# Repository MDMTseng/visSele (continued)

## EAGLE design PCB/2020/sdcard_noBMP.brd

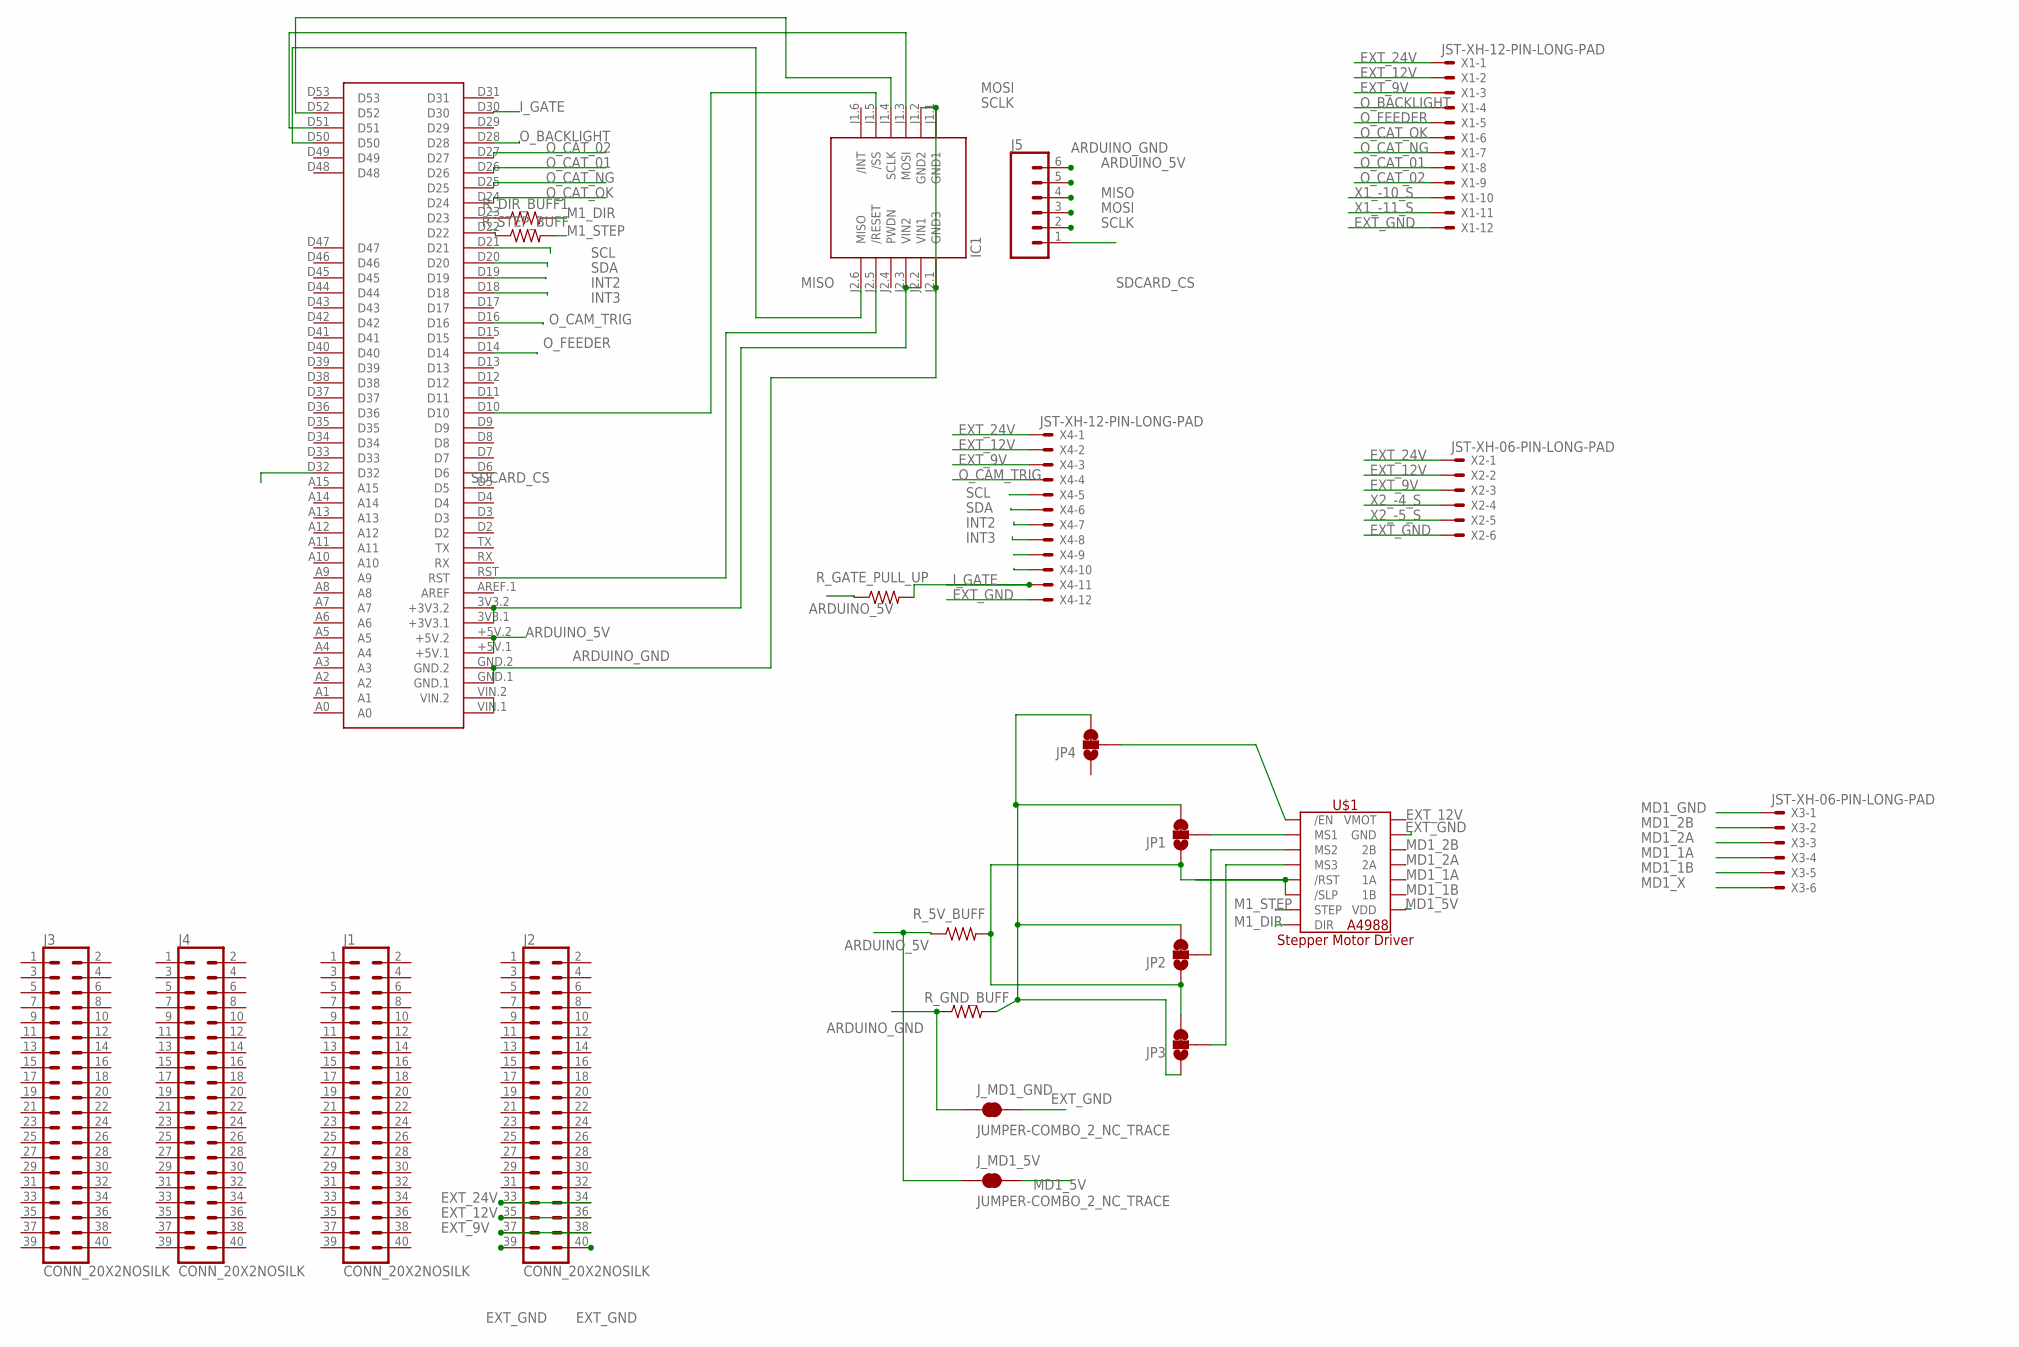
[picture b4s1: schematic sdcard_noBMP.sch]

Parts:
IC1: WIZ820IO_DEVICE'DUAL-IN-LINE'; WIZ820IO
J1, J2, J3, J4: CONN_20X2NOSILK; 2X20_NOSILK
J5: CONN_06LOCK; 1X06_LOCK
JP1, JP2, JP3, JP4: JUMPER-SMT_3_1-NC_TRACE_NO-SILK; SMT-JUMPER_3_1-NC_TRACE_NO-SILK
J_MD1_5V, J_MD1_GND: JUMPER-COMBO_2_NC_TRACE; COMBO-JUMPER_2_NC_TRACE
R_5V_BUFF: 1k; 0402-TIGHT
R_DIR_BUFF1: 1k; 0402-TIGHT
R_GATE_PULL_UP: 1k; 0402-TIGHT
R_GND_BUFF: 1k; 0402-TIGHT
R_STEP_BUFF: 1k; 0402-TIGHT
U$1: A4988_STEP
U$2: MEGA2560_MIKRO
X1, X4: JST-XH-12-PIN-LONG-PAD; JST-XH-12-PACKAGE-LONG-PAD
X2, X3: JST-XH-06-PIN-LONG-PAD; JST-XH-06-PACKAGE-LONG-PAD

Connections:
ARDUINO_5V: J5.5, J_MD1_5V.1, J_MD1_5V.3 (1), R_5V_BUFF.1, R_GATE_PULL_UP.1, U$2.+5V.1, U$2.+5V.2
ARDUINO_GND: IC1.J1.1 (GND1), IC1.J1.2 (GND2), IC1.J2.1 (GND3), J5.6, J_MD1_GND.1, J_MD1_GND.3 (1), R_GND_BUFF.1, U$2.GND.1, U$2.GND.2
EXT_9V: J2.37, J2.38, U$2.VIN.1, U$2.VIN.2, X1.3, X2.3, X4.3
EXT_12V: J2.35, J2.36, U$1.VMOT, X1.2, X2.2, X4.2
EXT_24V: J2.33, J2.34, X1.1, X2.1, X4.1
EXT_GND: J2.39, J2.40, J_MD1_GND.2, J_MD1_GND.4 (2), U$1.GND, U$1.GND2 (GND), X1.12, X2.6, X4.12
INT2: U$2.D19, X4.7
INT3: U$2.D18, X4.8
I_GATE: R_GATE_PULL_UP.2, U$2.D30, X4.11
M1_DIR: R_DIR_BUFF1.2, U$1.DIR
M1_STEP: R_STEP_BUFF.2, U$1.STEP
MD1_1A: U$1.1A, X3.4
MD1_1B: U$1.1B, X3.5
MD1_2A: U$1.2A, X3.3
MD1_2B: U$1.2B, X3.2
MD1_5V: J_MD1_5V.2, J_MD1_5V.4 (2), U$1.VDD
MD1_GND: X3.1
MD1_X: X3.6
MISO: IC1.J2.6 (MISO), J5.4, U$2.D50
MOSI: IC1.J1.3 (MOSI), J5.3, U$2.D51
unnamed: JP1.1, JP2.1, JP3.3, R_5V_BUFF.2, U$1./RST, U$1./SLP
unnamed: IC1.J1.5 (/SS), U$2.D10
unnamed: R_STEP_BUFF.1, U$2.D22
unnamed: IC1.J2.5 (/RESET), U$2.RST
unnamed: IC1.J2.2 (VIN1), IC1.J2.3 (VIN2), U$2.3V3.1 (+3V3.1), U$2.3V3.2 (+3V3.2)
unnamed: JP1.2, U$1.MS1
unnamed: JP2.2, U$1.MS2
unnamed: JP3.2, U$1.MS3
unnamed: JP4.2, U$1./EN
unnamed: JP1.3, JP2.3, JP3.1, JP4.3, R_GND_BUFF.2
unnamed: R_DIR_BUFF1.1, U$2.D23
O_BACKLIGHT: U$2.D28, X1.4
O_CAM_TRIG: U$2.D16, X4.4
O_CAT_01: U$2.D26, X1.8
O_CAT_02: U$2.D27, X1.9
O_CAT_NG: U$2.D25, X1.7
O_CAT_OK: U$2.D24, X1.6
O_FEEDER: U$2.D14, X1.5
SCL: U$2.D21, X4.5
SCLK: IC1.J1.4 (SCLK), J5.2, U$2.D52
SDA: U$2.D20, X4.6
SDCARD_CS: J5.1, U$2.D32
X1_-10_S: X1.10
X1_-11_S: X1.11
X2_-4_S: X2.4
X2_-5_S: X2.5

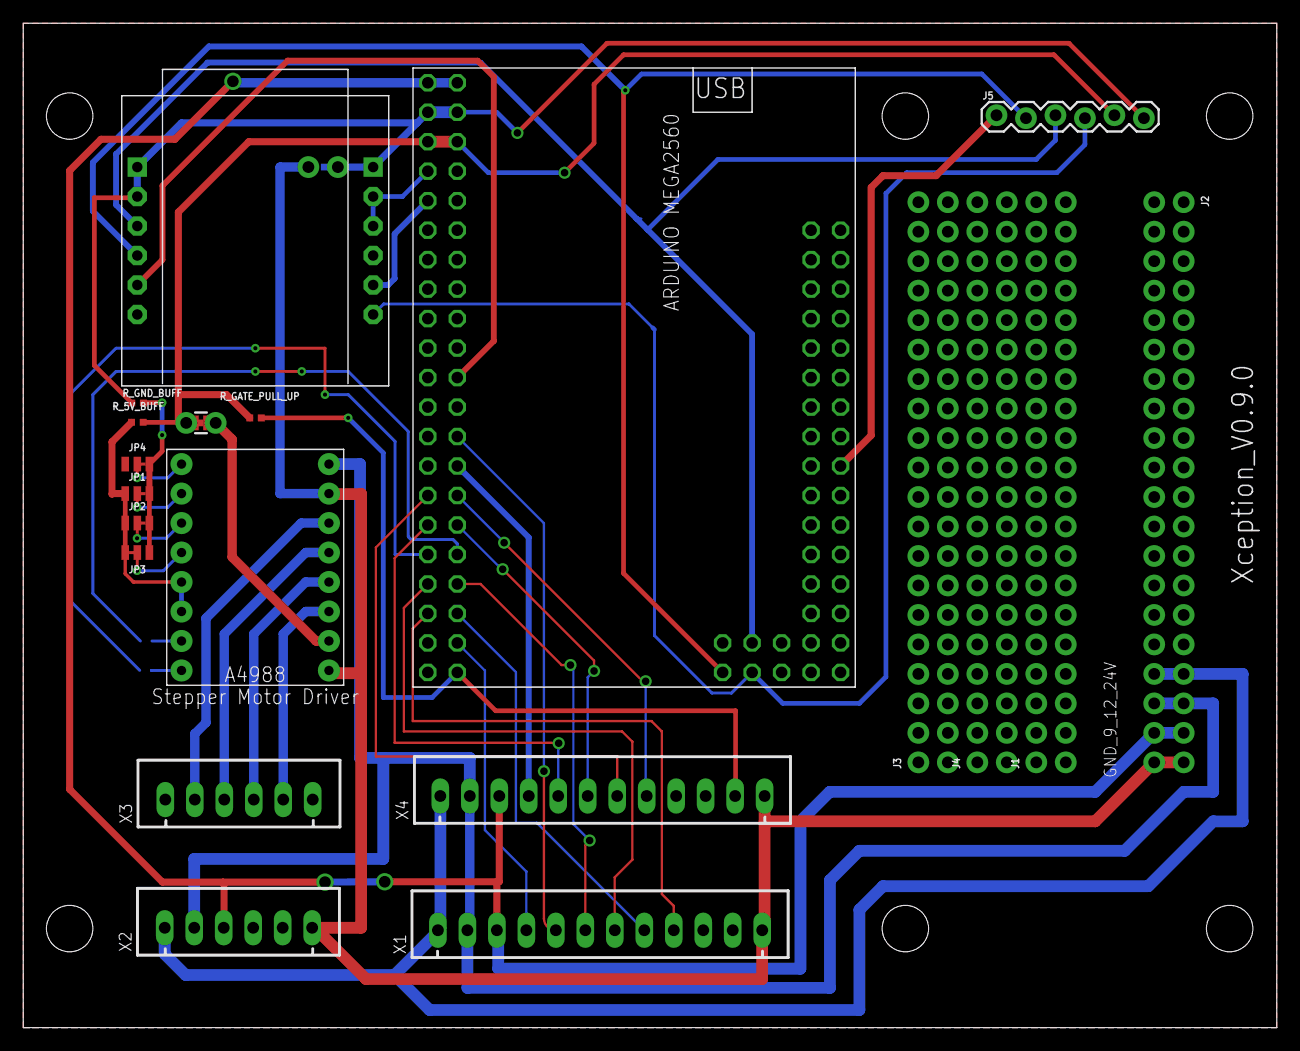
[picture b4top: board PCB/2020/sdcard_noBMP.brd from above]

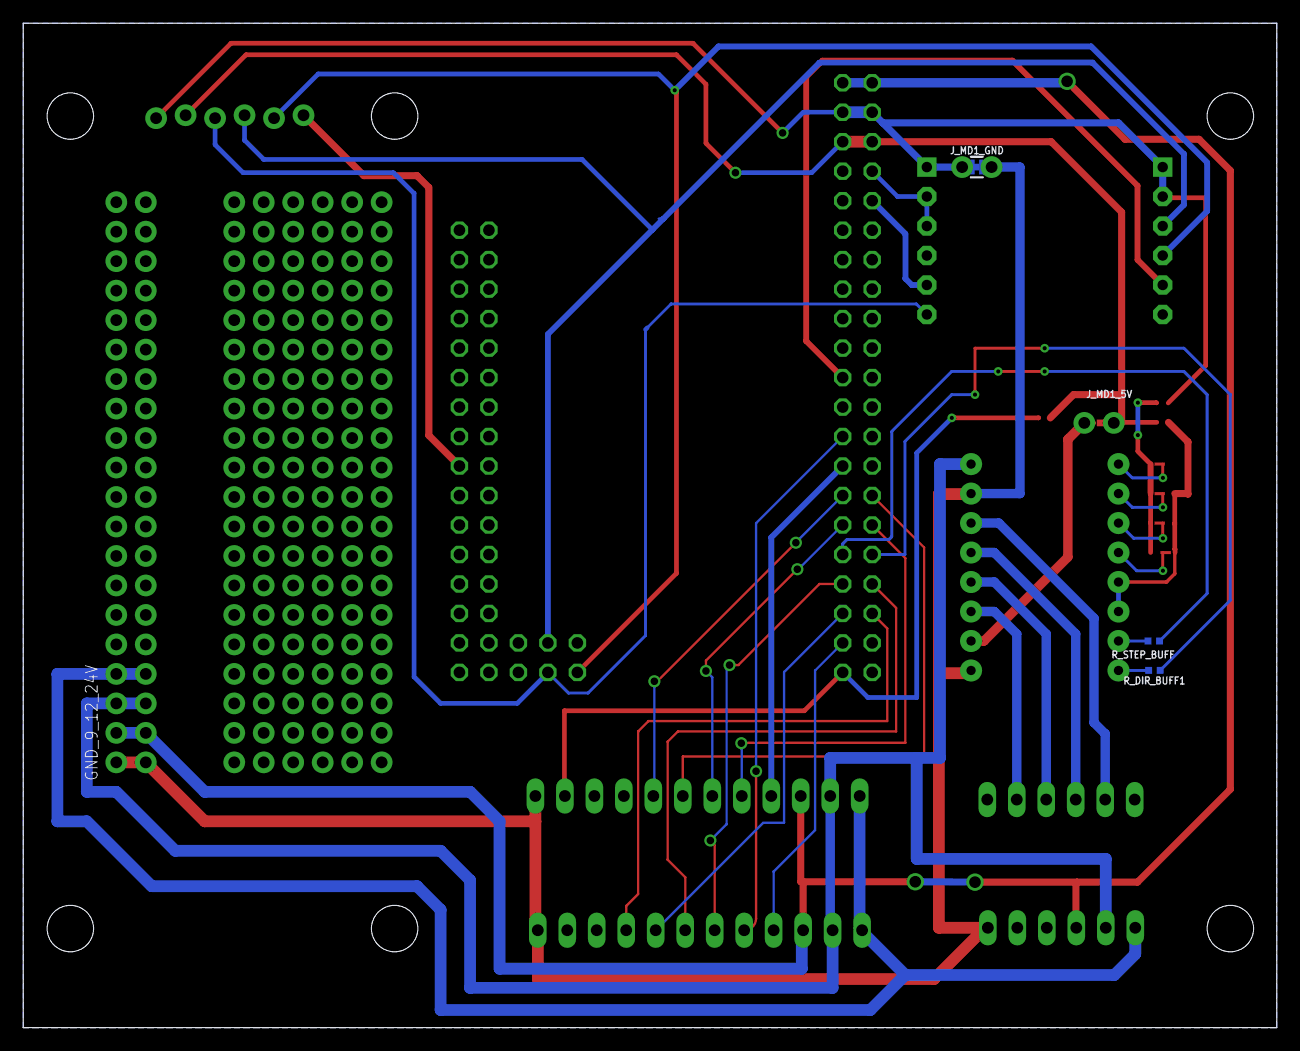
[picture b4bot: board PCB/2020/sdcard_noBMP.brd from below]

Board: 2 copper layers, 108.0 x 86.5 mm, 23 parts (3 on the bottom side), 40 nets.

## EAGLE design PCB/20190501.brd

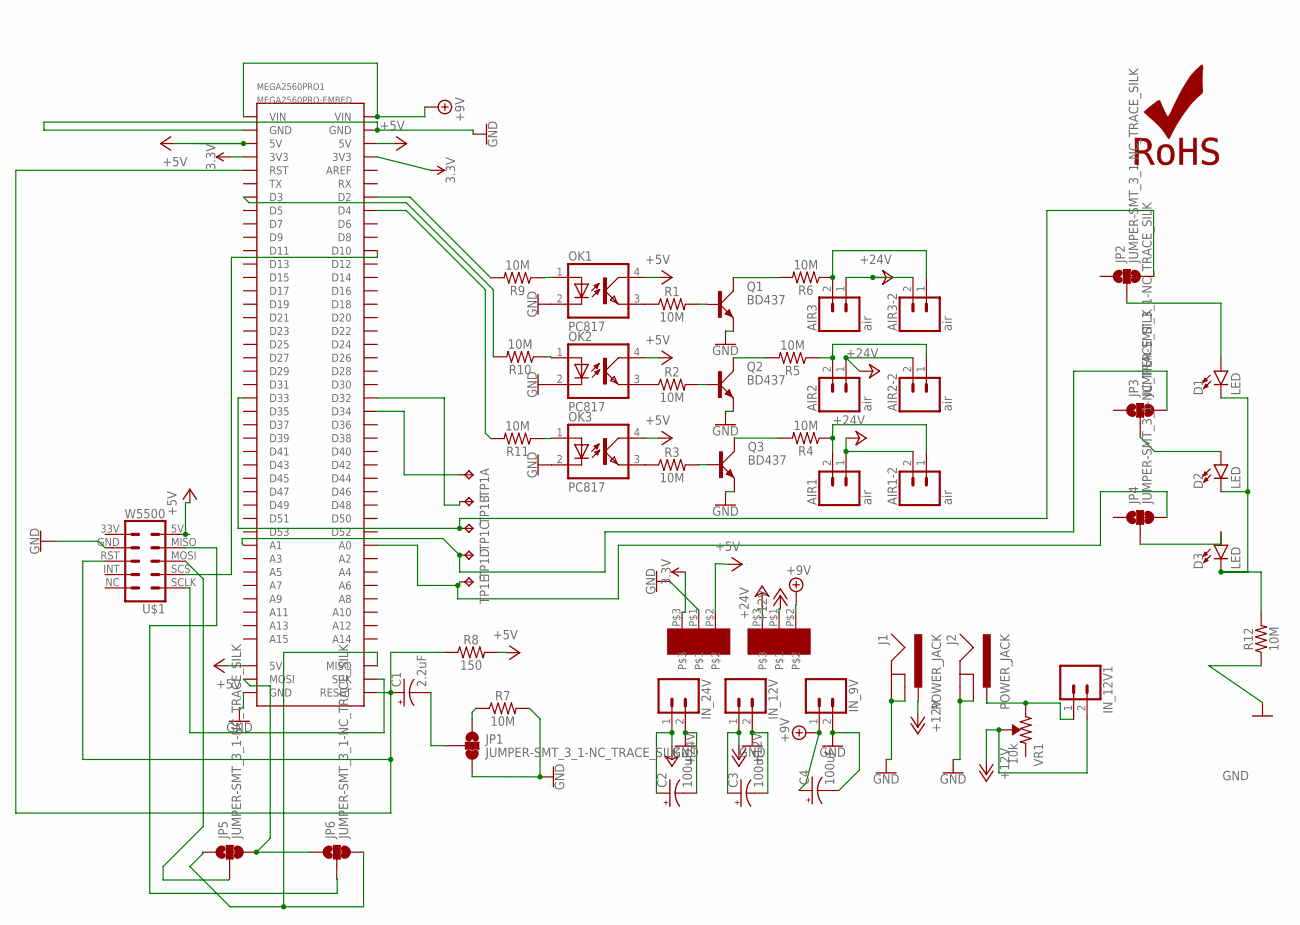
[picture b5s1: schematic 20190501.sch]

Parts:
AIR1, AIR2, AIR3: air; MOLEX-1X2_LOCK
AIR1-2, AIR2-2, AIR3-2: air; 1X02
C1: 2.2uF; CPOL-RADIAL-2.5MM-5MM-KIT
C2, C3, C4: 100uF; CPOL-RADIAL-2.5MM-6.5MM
D1, D2, D3: LED; LED_5MM
IN_9V, IN_12V, IN_12V1, IN_24V: CONN_02POLAR_LOCK; MOLEX-1X2_LOCK
J1, J2: POWER_JACK; POWER_JACK_PTH
JP1, JP2, JP3, JP4, JP5, JP6: JUMPER-SMT_3_1-NC_TRACE_SILK; SMT-JUMPER_3_1-NC_TRACE_SILK
LOGO1: ROHS_LOGO; ROHS_LOGO_0.18_IN
MEGA2560PRO1: MEGA2560PRO-EMBED
OK1, OK2, OK3: PC817; DIL04
Q1, Q2, Q3: BD437; TO126AV
R1, R2, R3, R4, R5, R6, R7, R9, R10, R11, R12: 10M; AXIAL-0.3
R8: 150; AXIAL-0.3
TP1: TP5P5-25-13; P5-25-13
U$1: W5500
U$2, U$4: AC_3PINAC3PIN7MM; AC3PIN7MM
VR1: 10k; TRIMPOT-PTH-3386U

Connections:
3.3V: MEGA2560PRO1.3V3@1 (3V3), MEGA2560PRO1.3V3@2 (3V3), U$4.P$3
+5V: MEGA2560PRO1.5V@1 (5V), MEGA2560PRO1.5V@2 (5V), MEGA2560PRO1.5V@3 (5V), OK1.4 (COL), OK2.4 (COL), OK3.4 (COL), R8.P$2 (2), U$1.5V (9), U$4.P$2
+9V: C4.1 (+), IN_9V.1, MEGA2560PRO1.VIN@1 (VIN), MEGA2560PRO1.VIN@2 (VIN), U$2.P$2
+12V: C3.1 (+), IN_12V.1, IN_12V1.2, J1.PWR, U$2.P$1, VR1.2 (WIPER)
+24V: AIR1.1, AIR1-2.2, AIR2.1, AIR2-2.2, AIR3.1, AIR3-2.2, C2.1 (+), IN_24V.1, U$2.P$3
GND: C2.2 (-), C3.2 (-), C4.2 (-), IN_9V.2, IN_12V.2, IN_24V.2, J1.GND, J1.GNDBREAK, J2.GND, J2.GNDBREAK, JP1.3, MEGA2560PRO1.GND@1 (GND), MEGA2560PRO1.GND@2 (GND), MEGA2560PRO1.GND@3 (GND), OK1.2 (C), OK2.2 (C), OK3.2 (C), Q1.E, Q2.E, Q3.E, R7.P$2 (2), R12.P$1 (1), U$1.GND (8), U$4.P$1
unnamed: Q1.C, R6.P$2 (2)
unnamed: Q2.C, R5.P$2 (2)
unnamed: Q3.C, R4.P$2 (2)
unnamed: AIR1.2, AIR1-2.1, R4.P$1 (1)
unnamed: AIR2.2, AIR2-2.1, R5.P$1 (1)
unnamed: AIR3.2, AIR3-2.1, R6.P$1 (1)
unnamed: OK1.3 (EMIT), R1.P$1 (1)
unnamed: OK2.3 (EMIT), R2.P$1 (1)
unnamed: OK3.3 (EMIT), R3.P$1 (1)
unnamed: Q3.B, R3.P$2 (2)
unnamed: Q2.B, R2.P$2 (2)
unnamed: Q1.B, R1.P$2 (2)
unnamed: C1.1 (+), MEGA2560PRO1.RESET, MEGA2560PRO1.RST, R8.P$1 (1), U$1.RST (6)
unnamed: C1.2 (-), JP1.2
unnamed: OK1.1 (A), R9.P$1 (1)
unnamed: MEGA2560PRO1.D3, R10.P$2 (2)
unnamed: OK2.1 (A), R10.P$1 (1)
unnamed: IN_12V1.1, J2.PWR, VR1.3 (CW)
unnamed: MEGA2560PRO1.D34, TP1.TP-1
unnamed: MEGA2560PRO1.D32, TP1.TP-2
unnamed: JP1.1, R7.P$1 (1)
unnamed: JP4.3, MEGA2560PRO1.A0, TP1.TP-5
unnamed: JP3.3, MEGA2560PRO1.A1, TP1.TP-4
unnamed: JP2.3, MEGA2560PRO1.D33, TP1.TP-3
unnamed: D1.K (C), D2.K (C), D3.K (C), R12.P$2 (2)
unnamed: D3.A, JP4.2
unnamed: OK3.1 (A), R11.P$1 (1)
unnamed: MEGA2560PRO1.D2, R9.P$2 (2)
unnamed: MEGA2560PRO1.D4, R11.P$2 (2)
unnamed: JP5.1, JP6.3, MEGA2560PRO1.MISO
unnamed: JP5.2, U$1.MOSI (5)
unnamed: MEGA2560PRO1.SCK, U$1.SCLK (33V)
unnamed: MEGA2560PRO1.D10, U$1.SCS (3)
unnamed: D2.A, JP3.2
unnamed: D1.A, JP2.2
unnamed: JP5.3, JP6.1, MEGA2560PRO1.MOSI
unnamed: JP6.2, U$1.MISO (7)

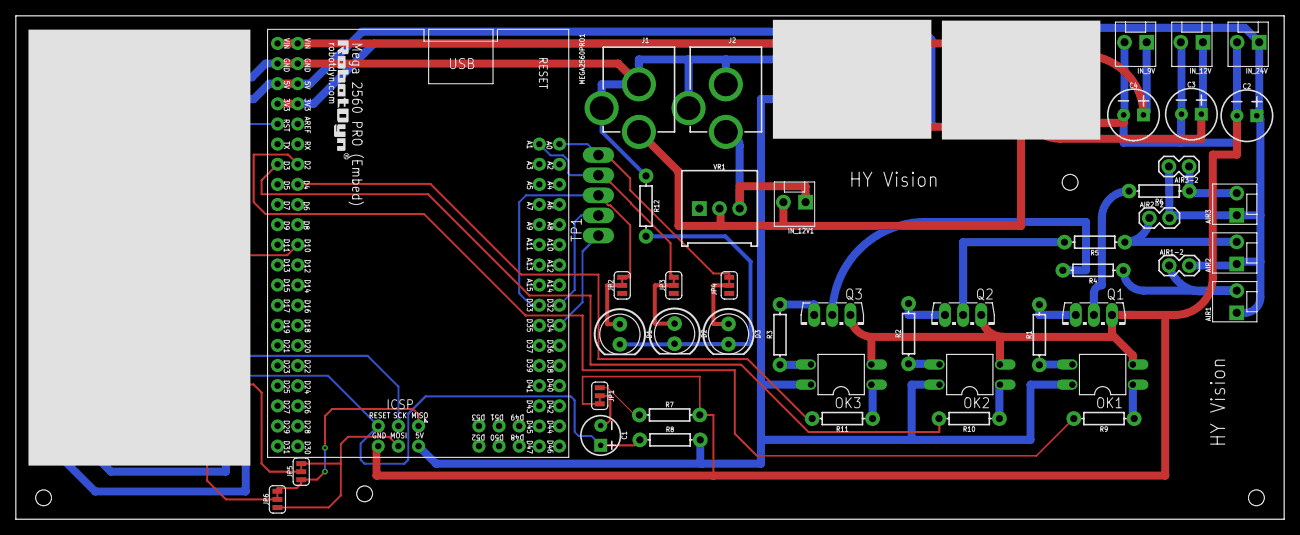
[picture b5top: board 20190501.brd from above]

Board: 2 copper layers, 160.0 x 63.5 mm, 50 parts (0 on the bottom side), 43 nets.

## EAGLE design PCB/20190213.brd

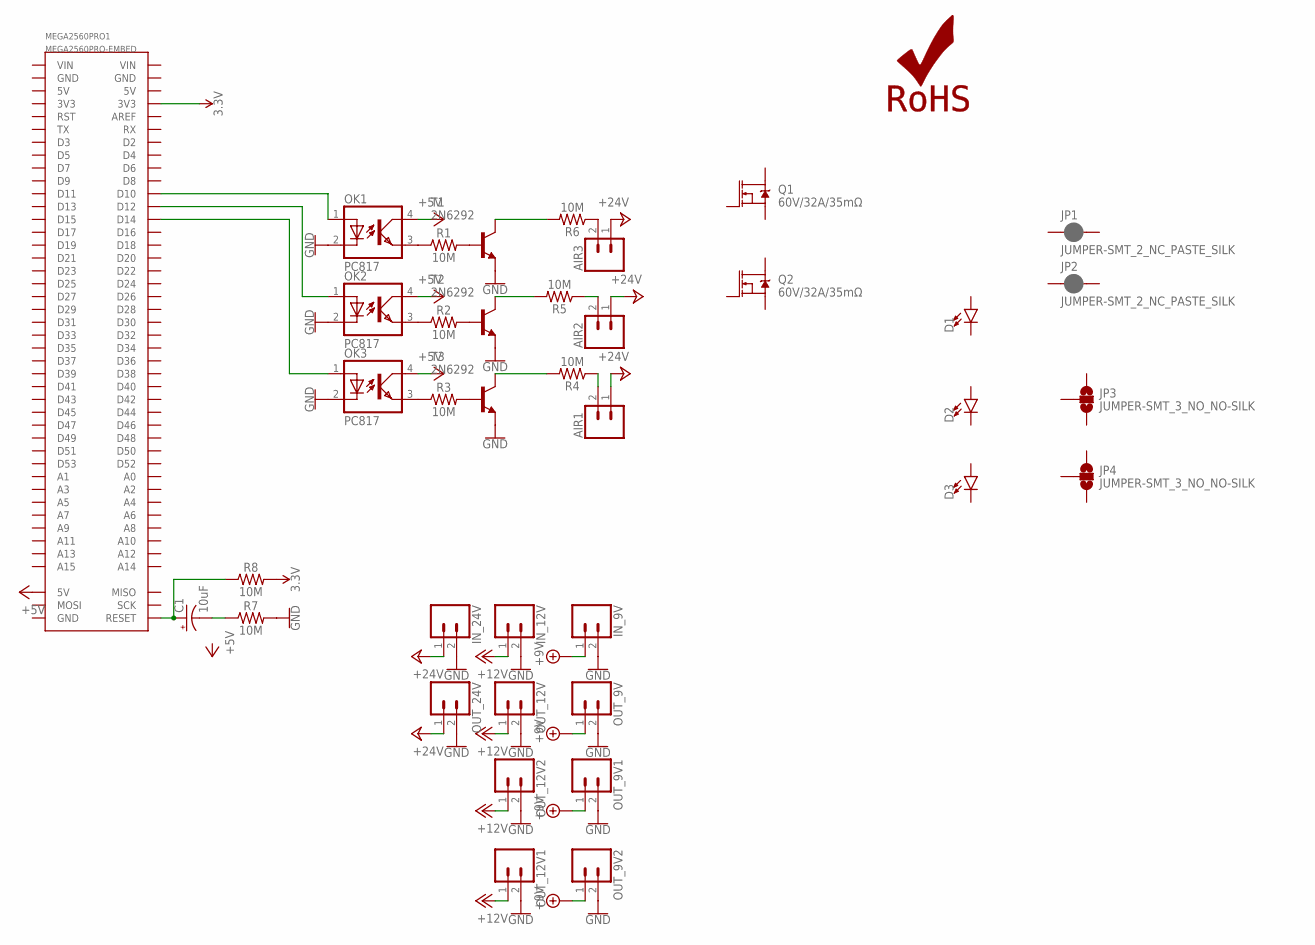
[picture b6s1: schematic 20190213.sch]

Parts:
AIR1, AIR2, AIR3: CONN_02POLAR_LOCK; MOLEX-1X2_LOCK
C1: 10uF; CPOL-RADIAL-2.5MM-5MM-KIT
D1, D2, D3: LED5MM; LED_5MM
IN_9V, IN_12V, IN_24V: CONN_02POLAR_LOCK; MOLEX-1X2_LOCK
JP1, JP2: JUMPER-SMT_2_NC_PASTE_SILK; SMT-JUMPER_2_NC_PASTE_SILK
JP3, JP4: JUMPER-SMT_3_NO_NO-SILK; SMT-JUMPER_3_NO_NO-SILK
LOGO1: ROHS_LOGO; ROHS_LOGO_0.18_IN
MEGA2560PRO1: MEGA2560PRO-EMBED
OK1, OK2, OK3: PC817; DIL04
OUT_9V, OUT_9V1, OUT_9V2, OUT_12V, OUT_12V1, OUT_12V2, OUT_24V: CONN_02POLAR_LOCK; MOLEX-1X2_LOCK
Q1, Q2: 60V/32A/35mΩ; TO220V
R1, R2, R3, R4, R5, R6, R7, R8: 10M; AXIAL-0.3
T1, T2, T3: 2N6292; TO220

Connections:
3.3V: MEGA2560PRO1.3V3@2 (3V3), R8.P$2 (2)
+5V: MEGA2560PRO1.5V@3 (5V), OK1.4 (COL), OK2.4 (COL), OK3.4 (COL)
+9V: IN_9V.1, OUT_9V.1, OUT_9V1.1, OUT_9V2.1
+12V: IN_12V.1, OUT_12V.1, OUT_12V1.1, OUT_12V2.1
+24V: AIR1.1, AIR2.1, AIR3.1, IN_24V.1, OUT_24V.1
GND: IN_9V.2, IN_12V.2, IN_24V.2, OK1.2 (C), OK2.2 (C), OK3.2 (C), OUT_9V.2, OUT_9V1.2, OUT_9V2.2, OUT_12V.2, OUT_12V1.2, OUT_12V2.2, OUT_24V.2, R7.P$2 (2), T1.3 (E), T2.3 (E), T3.3 (E)
unnamed: R1.P$2 (2), T1.1 (B)
unnamed: R2.P$2 (2), T2.1 (B)
unnamed: R3.P$2 (2), T3.1 (B)
unnamed: AIR1.2, R4.P$1 (1)
unnamed: AIR2.2, R5.P$1 (1)
unnamed: AIR3.2, R6.P$1 (1)
unnamed: OK1.3 (EMIT), R1.P$1 (1)
unnamed: OK2.3 (EMIT), R2.P$1 (1)
unnamed: OK3.3 (EMIT), R3.P$1 (1)
unnamed: R6.P$2 (2), T1.2 (C)
unnamed: R5.P$2 (2), T2.2 (C)
unnamed: R4.P$2 (2), T3.2 (C)
unnamed: C1.1 (+), MEGA2560PRO1.RESET, R8.P$1 (1)
unnamed: C1.2 (-), R7.P$1 (1)
unnamed: MEGA2560PRO1.D10, OK1.1 (A)
unnamed: MEGA2560PRO1.D12, OK2.1 (A)
unnamed: MEGA2560PRO1.D14, OK3.1 (A)

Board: 2 copper layers, 39 parts (0 on the bottom side), 23 nets, no tracks yet.
